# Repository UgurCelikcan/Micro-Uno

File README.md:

# Micro-Uno

A powerful, custom dual-microcontroller development board that combines the USB connectivity and compact form factor of the Pro Micro (`ATmega32U4`) with the classic pinout and versatility of the Arduino Uno (`ATmega328P`).

---

## 🚀 Key Features

* **Dual Microcontroller Architecture:**
  * **Core 1:** ATmega32U4 (`U1`) with native USB Type-C support, hardware serial, and HID capabilities.
  * **Core 2:** ATmega32P (`U2`) running with an external 16MHz crystal oscillator, providing classic Uno-compatible GPIO and analog channels.
* **Power & USB Interface:**
  * USB Type-C receptacle (`J1`) with CC1/CC2 pull-down resistors and a resettable PTC polyfuse (`F1`).
  * Comprehensive decoupling capacitance (`C1`-`C12`) ensuring stable power rails and clean clock signals.
* **Expansion & Connectivity:**
  * Dedicated ICSP headers (`J2`, `J3`) for direct programming of both microcontrollers.
  * Multi-pin breakout headers (`J4`, `J5`, `J6`) exposing full Port expansions (`PORTC`, `PORTD`, `PORTF`) for rapid prototyping.

---

## 📊 Schematic Overview

The schematic integrates both processor cores alongside robust power filtering and extensive pin breakout headers on a single A4 sheet.

---

## 🛠️ PCB Design & Routing

The PCB layout cleanly routes the dense dual-processor traces, keeping crystal oscillators close to their respective chips and managing power planes efficiently.

---

## 💡 3D Renders

### Top View

### Bottom View

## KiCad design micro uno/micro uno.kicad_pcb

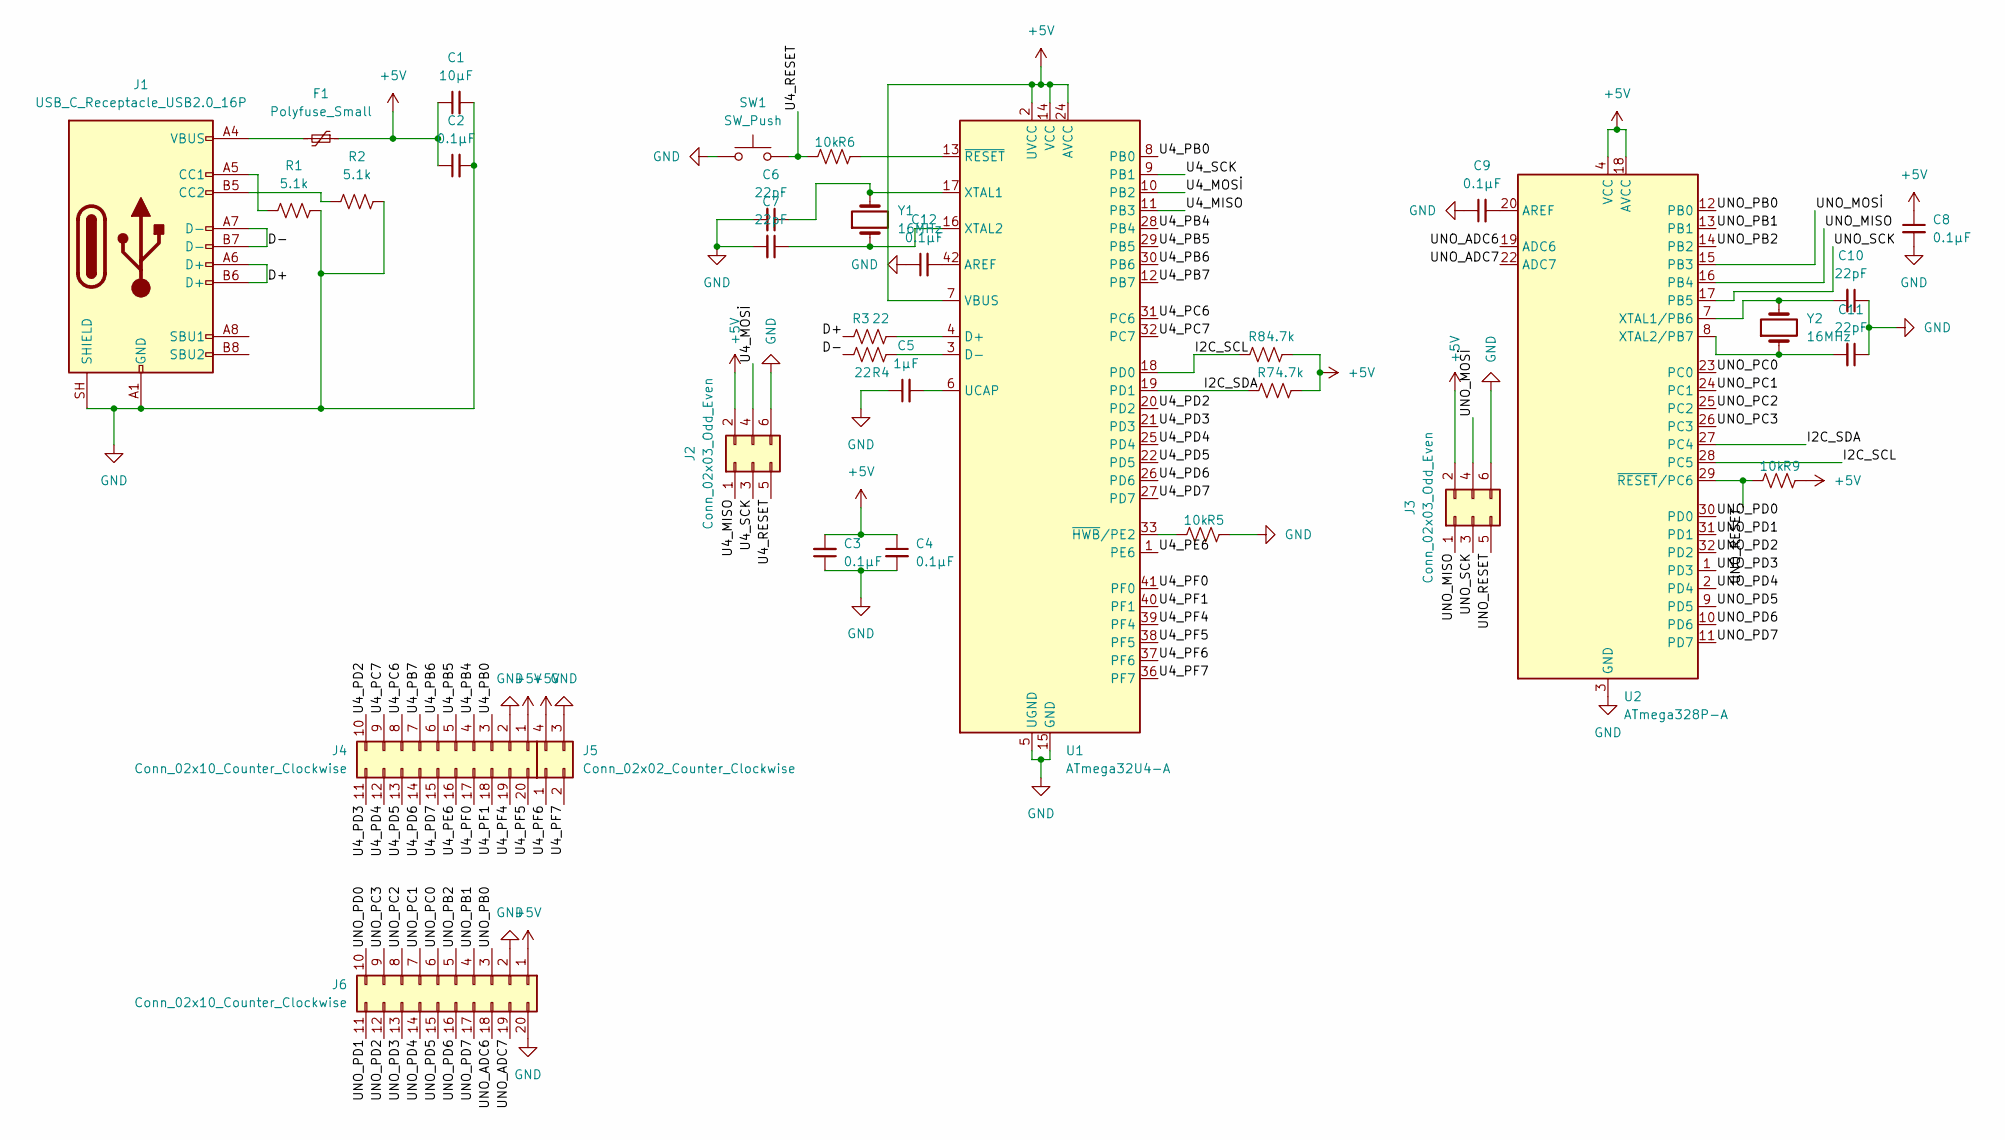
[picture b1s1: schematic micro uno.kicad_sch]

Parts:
C1: 10µF; C_1206_3216Metric
C2, C3, C4, C8, C9, C12: 0.1µF; C_0805_2012Metric
C5: 1µF; C_0805_2012Metric
C6, C7, C10, C11: 22pF; C_0805_2012Metric
F1: Polyfuse_Small; R_1206_3216Metric
J1: USB_C_Receptacle_USB2.0_16P; USB_C_Receptacle_HRO_TYPE-C-31-M-12
J2, J3: Conn_02x03_Odd_Even; PinHeader_2x03_P2.54mm_Vertical
J4, J6: Conn_02x10_Counter_Clockwise; PinHeader_2x10_P2.54mm_Vertical
J5: Conn_02x02_Counter_Clockwise; PinHeader_2x02_P2.54mm_Vertical
R1, R2: 5.1k; R_0805_2012Metric
R3, R4: 22; R_0805_2012Metric
R5, R6, R9: 10k; R_0805_2012Metric
R7, R8: 4.7k; R_0805_2012Metric
SW1: SW_Push; SW_SPST_PTS645Sx43SMTR92
U1: ATmega32U4-A; TQFP-44_10x10mm_P0.8mm
U2: ATmega328P-A; TQFP-32_7x7mm_P0.8mm
Y1, Y2: 16MHz; Crystal_SMD_3215-2Pin_3.2x1.5mm

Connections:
+5V: C1.1, C2.1, C3.2, C4.1, C8.1, F1.1, J2.2, J3.2, J4.1, J5.4, J6.1, R7.2, R8.2, R9.2, U1.2 (UVCC), U1.7 (VBUS), U1.14 (VCC), U1.24 (AVCC), U1.34 (VCC), U1.44 (AVCC), U2.4 (VCC), U2.6 (VCC), U2.18 (AVCC)
/D+: J1.A6 (D+), J1.B6 (D+), R3.1
/D-: J1.A7 (D-), J1.B7 (D-), R4.1
/I2C_SCL: R8.1, U1.18 (PD0), U2.28 (PC5)
/I2C_SDA: R7.1, U1.19 (PD1), U2.27 (PC4)
/U4_MISO: J2.1, U1.11 (PB3)
/U4_MOSİ: J2.4, U1.10 (PB2)
/U4_PB0: J4.3, U1.8 (PB0)
/U4_PB4: J4.4, U1.28 (PB4)
/U4_PB5: J4.5, U1.29 (PB5)
/U4_PB6: J4.6, U1.30 (PB6)
/U4_PB7: J4.7, U1.12 (PB7)
/U4_PC6: J4.8, U1.31 (PC6)
/U4_PC7: J4.9, U1.32 (PC7)
/U4_PD2: J4.10, U1.20 (PD2)
/U4_PD3: J4.11, U1.21 (PD3)
/U4_PD4: J4.12, U1.25 (PD4)
/U4_PD5: J4.13, U1.22 (PD5)
/U4_PD6: J4.14, U1.26 (PD6)
/U4_PD7: J4.15, U1.27 (PD7)
/U4_PE6: J4.16, U1.1 (PE6)
/U4_PF0: J4.17, U1.41 (PF0)
/U4_PF1: J4.18, U1.40 (PF1)
/U4_PF4: J4.19, U1.39 (PF4)
/U4_PF5: J4.20, U1.38 (PF5)
/U4_PF6: J5.1, U1.37 (PF6)
/U4_PF7: J5.2, U1.36 (PF7)
/U4_RESET: J2.5, R6.1, SW1.2
/U4_SCK: J2.3, U1.9 (PB1)
/UNO_ADC6: J6.18, U2.19 (ADC6)
/UNO_ADC7: J6.19, U2.22 (ADC7)
/UNO_MISO: J3.1, U2.16 (PB4)
/UNO_MOSİ: J3.4, U2.15 (PB3)
/UNO_PB0: J6.3, U2.12 (PB0)
/UNO_PB1: J6.4, U2.13 (PB1)
/UNO_PB2: J6.5, U2.14 (PB2)
/UNO_PC0: J6.6, U2.23 (PC0)
/UNO_PC1: J6.7, U2.24 (PC1)
/UNO_PC2: J6.8, U2.25 (PC2)
/UNO_PC3: J6.9, U2.26 (PC3)
/UNO_PD0: J6.10, U2.30 (PD0)
/UNO_PD1: J6.11, U2.31 (PD1)
/UNO_PD2: J6.12, U2.32 (PD2)
/UNO_PD3: J6.13, U2.1 (PD3)
/UNO_PD4: J6.14, U2.2 (PD4)
/UNO_PD5: J6.15, U2.9 (PD5)
/UNO_PD6: J6.16, U2.10 (PD6)
/UNO_PD7: J6.17, U2.11 (PD7)
/UNO_RESET: J3.5, R9.1, U2.29 (~RESET/PC6)
/UNO_SCK: J3.3, U2.17 (PB5)
GND: C1.2, C2.2, C3.1, C4.2, C5.1, C6.2, C7.2, C8.2, C9.1, C10.1, C11.1, C12.1, J1.A1 (GND), J1.A12 (GND), J1.B1 (GND), J1.B12 (GND), J1.SH (SHIELD), J2.6, J3.6, J4.2, J5.3, J6.2, J6.20, R1.2, R2.2, R5.2, SW1.1, U1.5 (UGND), U1.15 (GND), U1.23 (GND), U1.35 (GND), U1.43 (GND), U2.3 (GND), U2.5 (GND), U2.21 (GND)
unnamed: F1.2, J1.A4 (VBUS), J1.A9 (VBUS), J1.B4 (VBUS), J1.B9 (VBUS)
unnamed: J1.A5 (CC1), R1.1
unnamed: J1.B5 (CC2), R2.1
unnamed: C12.2, U1.42 (AREF)
unnamed: R3.2, U1.4 (D+)
unnamed: R4.2, U1.3 (D-)
unnamed: C5.2, U1.6 (UCAP)
unnamed: C6.1, U1.17 (XTAL1), Y1.2
unnamed: C7.1, U1.16 (XTAL2), Y1.1
unnamed: R5.1, U1.33 (~HWB/PE2)
unnamed: R6.2, U1.13 (~RESET)
unnamed: C9.2, U2.20 (AREF)
unnamed: C10.2, U2.7 (XTAL1/PB6), Y2.2
unnamed: C11.2, U2.8 (XTAL2/PB7), Y2.1

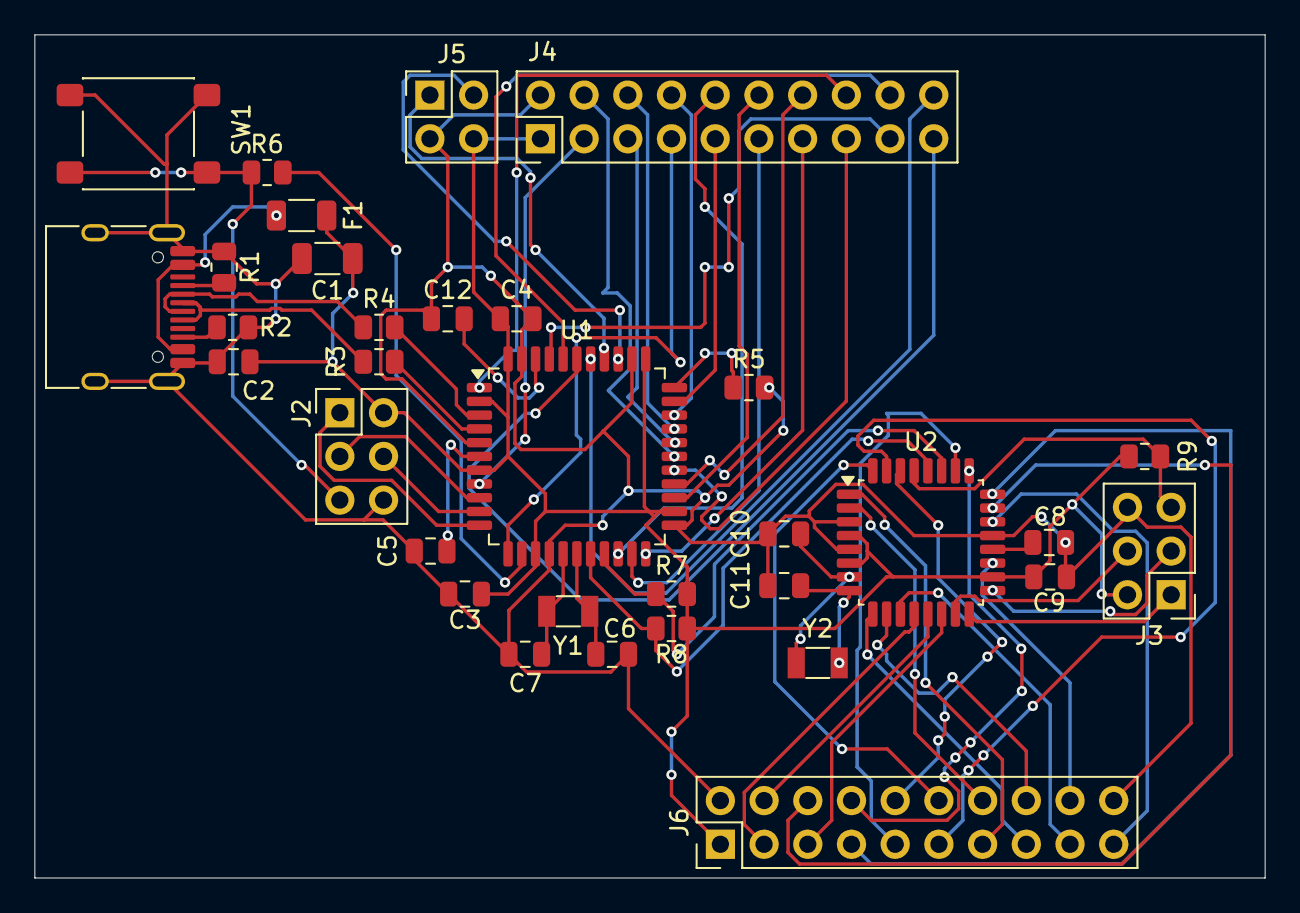
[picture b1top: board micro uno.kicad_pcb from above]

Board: 2 copper layers, 71.5 x 49.0 mm, 33 parts (0 on the bottom side), 65 nets.
